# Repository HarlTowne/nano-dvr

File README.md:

Trying to make an ultra-small & ultra-light DVR board for FPV tinywhoops.

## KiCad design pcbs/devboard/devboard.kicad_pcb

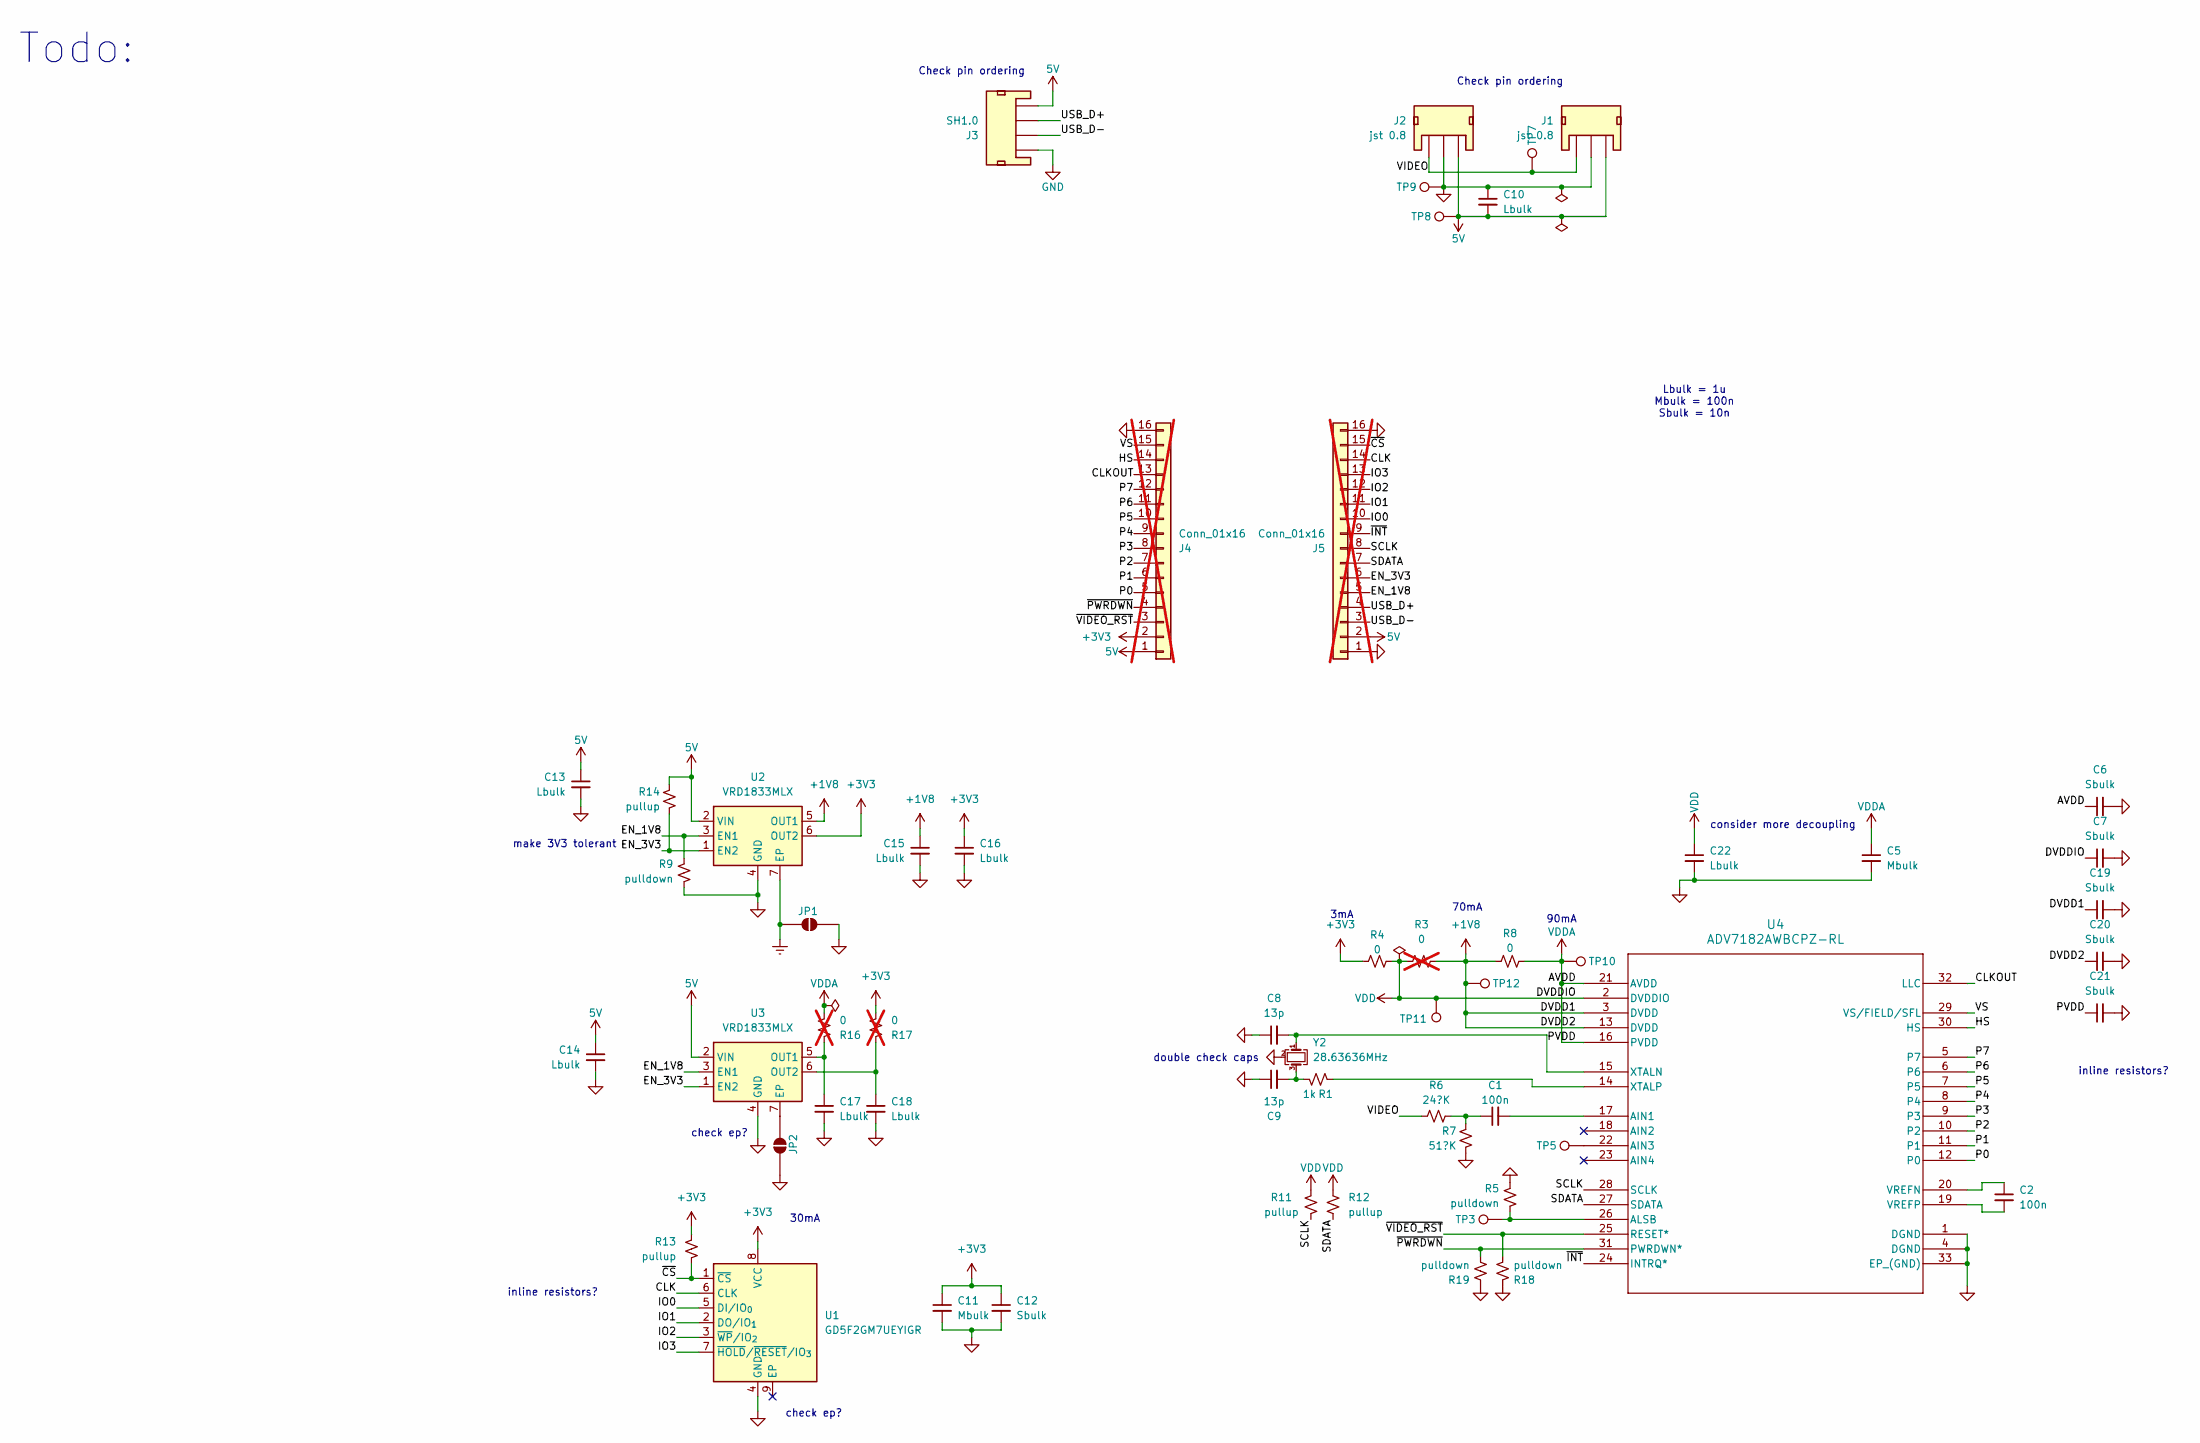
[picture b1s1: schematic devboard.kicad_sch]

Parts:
C1, C2: 100n; C_0402_1005Metric; JLC Part Number C1525
C5, C11: Mbulk; C_0402_1005Metric; JLC Part Number C1525
C6, C7, C12, C19, C20, C21: Sbulk; C_0402_1005Metric; JLC Part Number C15195
C8, C9: 13p; C_0402_1005Metric; JLC Part Number C20041963
C10, C13, C14, C15, C16, C17, C18, C22: Lbulk; C_0402_1005Metric; JLC Part Number C23733
J1, J2: jst 0.8; JST_SUR_SM03B-SURS-TF_1x03-1MP_P0.80mm_Horizontal; JLC Part Number C265338
J3: SH1.0; JST_SH_SM04B-SRSS-TB_1x04-1MP_P1.00mm_Horizontal; JLC Part Number C160404
J4, J5: Conn_01x16; PinSocket_1x16_P2.54mm_Vertical; not fitted
JP1, JP2: SolderJumper_2_Open; SolderJumper-2_P1.3mm_Open_Pad1.0x1.5mm
R1: 1k; R_0402_1005Metric; JLC Part Number C11702
R3, R16, R17: 0; R_0402_1005Metric; JLC Part Number C17168; not fitted
R4, R8: 0; R_0402_1005Metric; JLC Part Number C17168
R5, R9, R18, R19: pulldown; R_0402_1005Metric; JLC Part Number C881131
R6: 24?K; R_0402_1005Metric; JLC Part Number C2909331
R7: 51?K; R_0402_1005Metric; JLC Part Number C881131
R11, R12, R13, R14: pullup; R_0402_1005Metric; JLC Part Number C881131
TP3, TP5, TP7, TP8, TP9, TP10, TP11, TP12: TestPoint; TestPoint_Pad_D1.0mm
U1: GD5F2GM7UEYIGR; WSON-8-1EP_8x6mm_P1.27mm_EP3.4x4.3mm; JLC Part Number C22412867
U2, U3: VRD1833MLX; LLP-6; JLC Part Number C697928
U4: ADV7182AWBCPZ-RL; LFCSP-32-1EP_5x5mm_P0.5mm_EP3.6x3.6mm_ThermalVias; JLC Part Number C662245
Y2: 28.63636MHz; Crystal_SMD_3225-4Pin_3.2x2.5mm; JLC Part Number C7302014

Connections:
5V: C10.2, C13.1, C14.1, J1.1, J2.1, J3.4, J4.1, J5.2, R14.2, TP8.1 (1_1), U2.2 (VIN), U3.2 (VIN)
+1V8: C15.1, C19.1, C20.1, R3.2, R8.1, TP12.1 (1_1), U2.5 (OUT1), U4.3 (DVDD), U4.13 (DVDD)
+3V3: C11.1, C12.1, C16.1, J4.2, R4.1, R13.2, R17.1, U1.8 (VCC), U2.6 (OUT2)
/CLK: J5.14, U1.6 (CLK)
/CLKOUT: J4.13, U4.32 (LLC)
/EN_1V8: J5.5, R9.2, U2.3 (EN1), U3.3 (EN1)
/EN_3V3: J5.6, R14.1, U2.1 (EN2), U3.1 (EN2)
/HS: J4.14, U4.30 (HS)
/IO0: J5.10, U1.5 (DI/IO_{0})
/IO1: J5.11, U1.2 (DO/IO_{1})
/IO2: J5.12, U1.3 (~WP/IO_{2})
/IO3: J5.13, U1.7 (~HOLD/~RESET/IO_{3})
/P0: J4.5, U4.12 (P0)
/P1: J4.6, U4.11 (P1)
/P2: J4.7, U4.10 (P2)
/P3: J4.8, U4.9 (P3)
/P4: J4.9, U4.8 (P4)
/P5: J4.10, U4.7 (P5)
/P6: J4.11, U4.6
/P7: J4.12, U4.5 (P7)
/SCLK: J5.8, R11.2, U4.28 (SCLK)
/SDATA: J5.7, R12.1, U4.27 (SDATA)
/USB_D+: J3.3, J5.4
/USB_D-: J3.2, J5.3
/VIDEO: J1.3, J2.3, R6.1, TP7.1 (1_1)
/VS: J4.15, U4.29 (VS/FIELD/SFL)
/~CS: J5.15, R13.1, U1.1 (~CS)
/~INT: J5.9, U4.24 (INTRQ*)
/~PWRDWN: J4.4, R19.1, U4.31 (PWRDWN*)
/~VIDEO_RST: J4.3, R18.1, U4.25 (RESET*)
Earth: JP1.1 (A), U2.7 (EP)
GND: C5.2, C6.2, C7.2, C8.1, C9.1, C10.1, C11.2, C12.2, C13.2, C14.2, C15.2, C16.2, C17.2, C18.2, C19.2, C20.2, C21.2, C22.2, J1.2, J2.2, J3.1, J4.16, J5.1, J5.16, JP1.2 (B), JP2.2 (B), R5.2, R7.2, R9.1, R18.2, R19.2, TP9.1 (1_1), U1.4 (GND), U2.4 (GND), U3.4 (GND), U4.1 (DGND), U4.4 (DGND), U4.33 (EP_(GND)), Y2.2 (G), Y2.4 (G)
unnamed: C1.1, R6.2, R7.1
unnamed: C9.2, R1.1, Y2.3
unnamed: JP2.1 (A), U3.7 (EP)
unnamed: C17.1, R16.2, U3.5 (OUT1)
unnamed: C18.1, R17.2, U3.6 (OUT2)
unnamed: C1.2, U4.17 (AIN1)
unnamed: TP5.1 (1_1), U4.22 (AIN3)
unnamed: R5.1, TP3.1 (1_1), U4.26 (ALSB)
unnamed: C2.1, U4.20 (VREFN)
unnamed: C2.2, U4.19 (VREFP)
unnamed: C8.2, U4.15 (XTALN), Y2.1
unnamed: R1.2, U4.14 (XTALP)
VDD: C7.1, C22.1, R3.1, R4.2, R11.1, R12.2, TP11.1 (1_1), U4.2 (DVDDIO)
VDDA: C5.1, C6.1, C21.1, R8.2, R16.1, TP10.1 (1_1), U4.16 (PVDD), U4.21 (AVDD)

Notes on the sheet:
Check pin ordering
check ep?
70mA
3mA
make 3V3 tolerant
consider more decoupling
90mA
Lbulk = 1u Mbulk = 100n Sbulk = 10n
inline resistors?
double check caps
Todo:
30mA

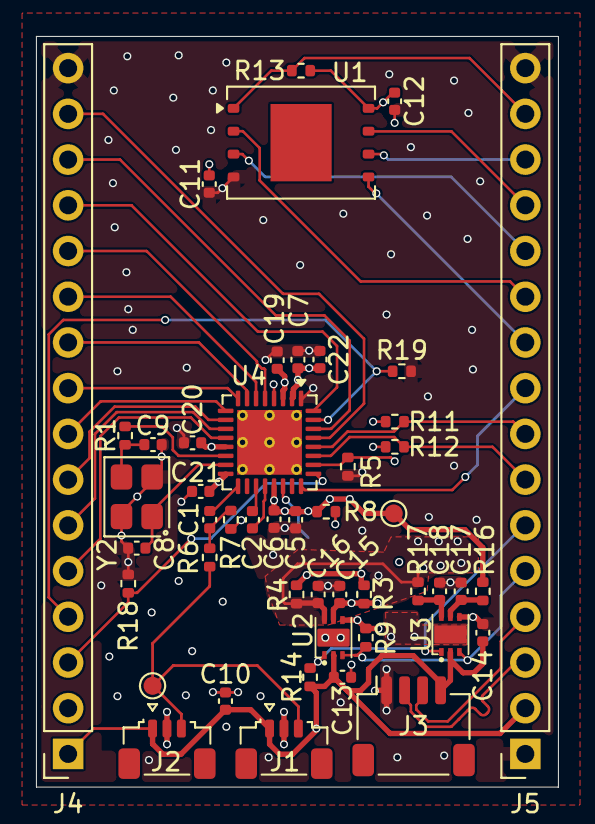
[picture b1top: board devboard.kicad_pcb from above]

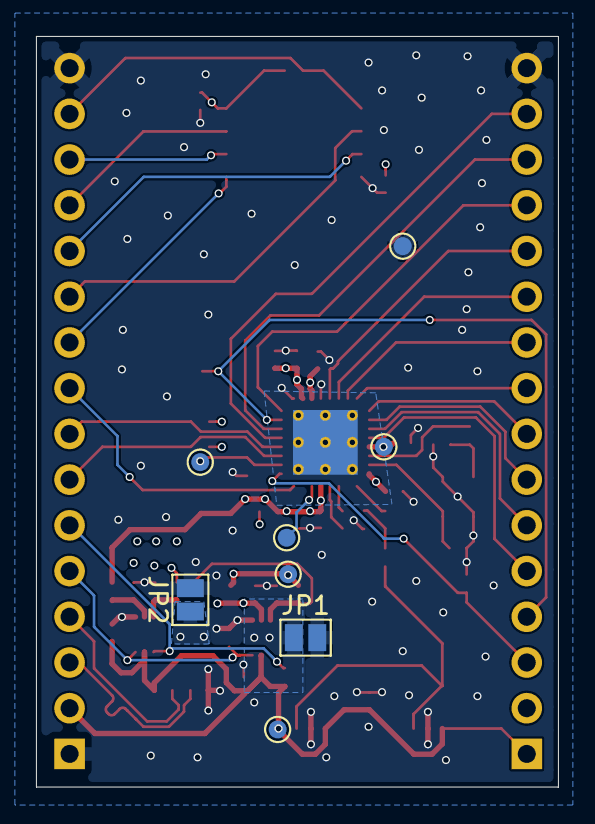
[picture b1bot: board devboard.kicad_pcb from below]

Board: 4 copper layers, 29.0 x 41.7 mm, 56 parts (8 on the bottom side), 46 nets.

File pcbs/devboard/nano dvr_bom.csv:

"Reference","Value","JLC Part Number","Footprint","Qty"
"U1","GD5F2GM7UEYIGR","C22412867 ","Package_SON:WSON-8-1EP_8x6mm_P1.27mm_EP3.4x4.3mm","1"
"Y2","28.63636MHz","C7302014","PCM_Crystal_AKL:Crystal_SMD_3225-4Pin_3.2x2.5mm","1"
"R6","24?K","C2909331","Resistor_SMD:R_0402_1005Metric","1"
"R11,R12,R13,R14","pullup","C881131","Resistor_SMD:R_0402_1005Metric","4"
"R7","51?K","C881131","Resistor_SMD:R_0402_1005Metric","1"
"R5,R9,R18,R19","pulldown","C881131","Resistor_SMD:R_0402_1005Metric","4"
"U2,U3","VRD1833MLX","C697928","LLP-6:LLP-6","2"
"U4","ADV7182AWBCPZ-RL","C662245","Package_CSP:LFCSP-32-1EP_5x5mm_P0.5mm_EP3.6x3.6mm_ThermalVias","1"
"C8,C9","13p","C597181","Capacitor_SMD:C_0402_1005Metric","2"
"J1,J2","jst 0.8","C265338 ","Connector_JST:JST_SUR_SM03B-SURS-TF_1x03-1MP_P0.80mm_Horizontal","2"
"J3","SH1.0","C160404","Connector_JST:JST_SH_SM04B-SRSS-TB_1x04-1MP_P1.00mm_Horizontal","1"
"C10,C13,C14,C15,C16,C17,C18,C22","Lbulk","C23733","Capacitor_SMD:C_0402_1005Metric","8"
"R3,R4,R8,R16,R17","0","C17168","Resistor_SMD:R_0402_1005Metric","5"
"C6,C7,C12,C19,C20,C21","Sbulk","C15195","Capacitor_SMD:C_0402_1005Metric","6"
"R1","1k","C11702","Resistor_SMD:R_0402_1005Metric","1"
"C5,C11","Mbulk","C1525 ","Capacitor_SMD:C_0402_1005Metric","2"
"C1,C2","100n","C1525 ","Capacitor_SMD:C_0402_1005Metric","2"
"TP3,TP5,TP7,TP8,TP9,TP10,TP11,TP12","TestPoint","","TestPoint:TestPoint_Pad_D1.0mm","8"
"J4,J5","Conn_01x16","","Connector_PinSocket_2.54mm:PinSocket_1x16_P2.54mm_Vertical","2"
